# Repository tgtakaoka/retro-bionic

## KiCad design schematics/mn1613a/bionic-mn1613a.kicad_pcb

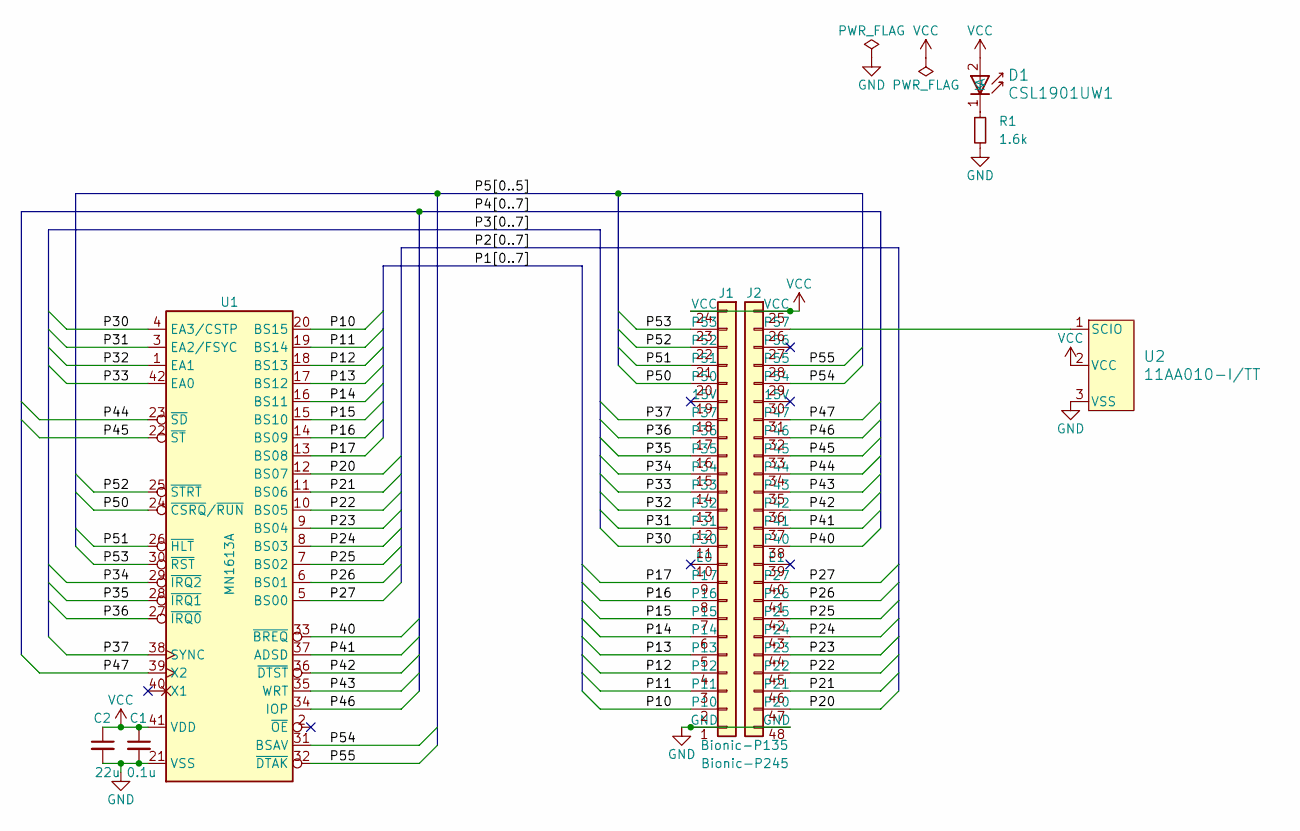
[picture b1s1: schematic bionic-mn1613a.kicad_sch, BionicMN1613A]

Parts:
C1: 0.1u; C_0603_1608Metric_Pad1.08x0.95mm_HandSolder
C2: 22u; C_0603_1608Metric_Pad1.08x0.95mm_HandSolder
D1: CSL1901UW1; LED_CSL1901UW1_ROM-M
J1: Bionic-P135; Bionic-P135_Vertical
J2: Bionic-P245; Bionic-P245_Vertical
R1: 1.6k; R_0603_1608Metric_Pad0.98x0.95mm_HandSolder
U1: MN1613A; DIP-42_W15.24mm_Socket
U2: 11AA010-I/TT; SOT-23_MC_MCH-M

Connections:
/P10: J1.2 (P10), U1.20 (BS15)
/P11: J1.3 (P11), U1.19 (BS14)
/P12: J1.4 (P12), U1.18 (BS13)
/P13: J1.5 (P13), U1.17 (BS12)
/P14: J1.6 (P14), U1.16 (BS11)
/P15: J1.7 (P15), U1.15 (BS10)
/P16: J1.8 (P16), U1.14 (BS09)
/P17: J1.9 (P17), U1.13 (BS08)
/P20: J2.47 (P20), U1.12 (BS07)
/P21: J2.46 (P21), U1.11 (BS06)
/P22: J2.45 (P22), U1.10 (BS05)
/P23: J2.44 (P23), U1.9 (BS04)
/P24: J2.43 (P24), U1.8 (BS03)
/P25: J2.42 (P25), U1.7 (BS02)
/P26: J2.41 (P26), U1.6 (BS01)
/P27: J2.40 (P27), U1.5 (BS00)
/P30: J1.11 (P30), U1.4 (EA3/CSTP)
/P31: J1.12 (P31), U1.3 (EA2/FSYC)
/P32: J1.13 (P32), U1.1 (EA1)
/P33: J1.14 (P33), U1.42 (EA0)
/P34: J1.15 (P34), U1.29 (~IRQ2)
/P35: J1.16 (P35), U1.28 (~IRQ1)
/P36: J1.17 (P36), U1.27 (~IRQ0)
/P37: J1.18 (P37), U1.38 (SYNC)
/P40: J2.38 (P40), U1.33 (~BREQ)
/P41: J2.37 (P41), U1.37 (ADSD)
/P42: J2.36 (P42), U1.36 (~DTST)
/P43: J2.35 (P43), U1.35 (WRT)
/P44: J2.34 (P44), U1.23 (~SD)
/P45: J2.33 (P45), U1.22 (~ST)
/P46: J2.32 (P46), U1.34 (IOP)
/P47: J2.31 (P47), U1.39 (X2)
/P50: J1.20 (P50), U1.24 (~CSRQ/~RUN)
/P51: J1.21 (P51), U1.26 (~HLT)
/P52: J1.22 (P52), U1.25 (~STRT)
/P53: J1.23 (P53), U1.30 (~RST)
/P54: J2.29 (P54), U1.31 (BSAV)
/P55: J2.28 (P55), U1.32 (~DTAK)
GND: C1.2, C2.2, J1.1 (GND), J2.48 (GND), R1.2, U1.21 (VSS), U2.3 (VSS)
unnamed: D1.1 (K), R1.1
unnamed: J2.26 (P57), U2.1 (SCIO)
VCC: C1.1, C2.1, D1.2 (A), J1.24 (VCC), J2.25 (VCC), U1.41 (VDD), U2.2 (VCC)

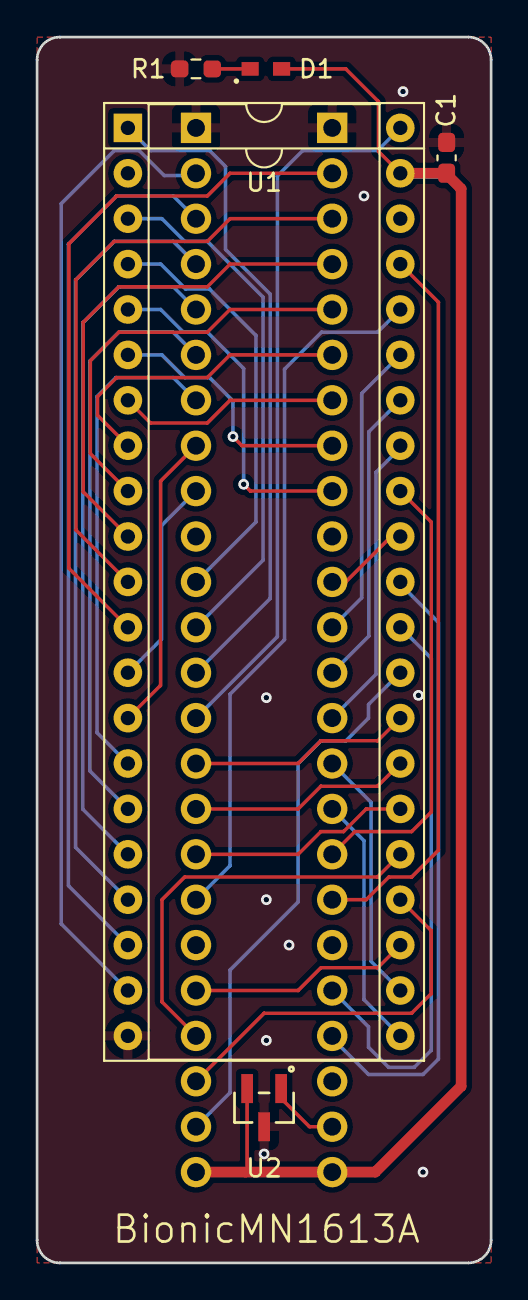
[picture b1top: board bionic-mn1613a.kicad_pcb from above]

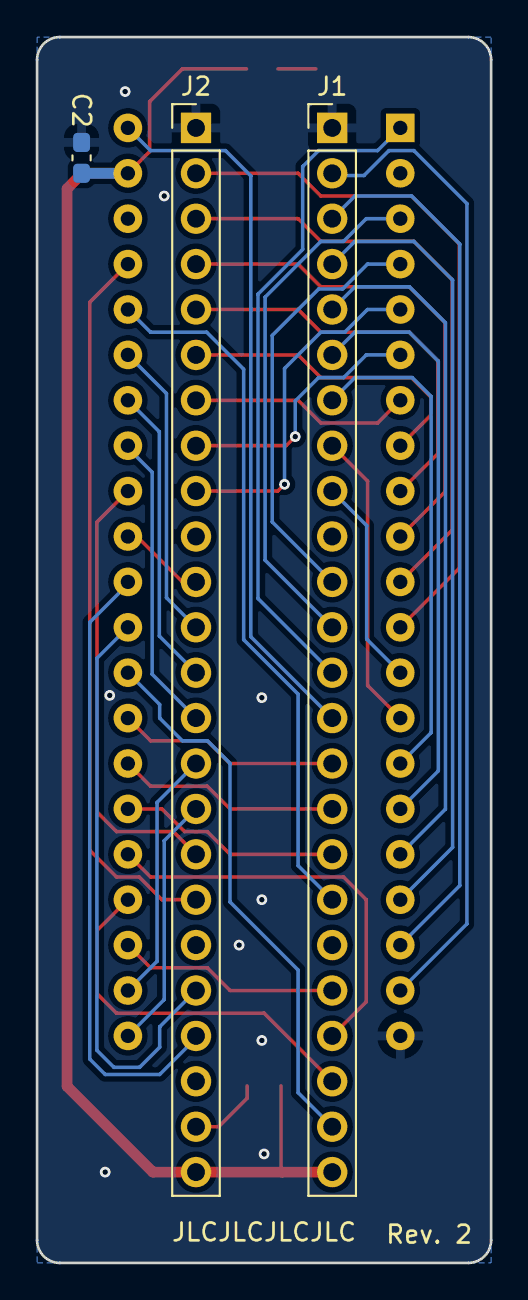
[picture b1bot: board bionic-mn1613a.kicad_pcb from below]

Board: 2 copper layers, 25.4 x 68.6 mm, 8 parts (3 on the bottom side), 42 nets.

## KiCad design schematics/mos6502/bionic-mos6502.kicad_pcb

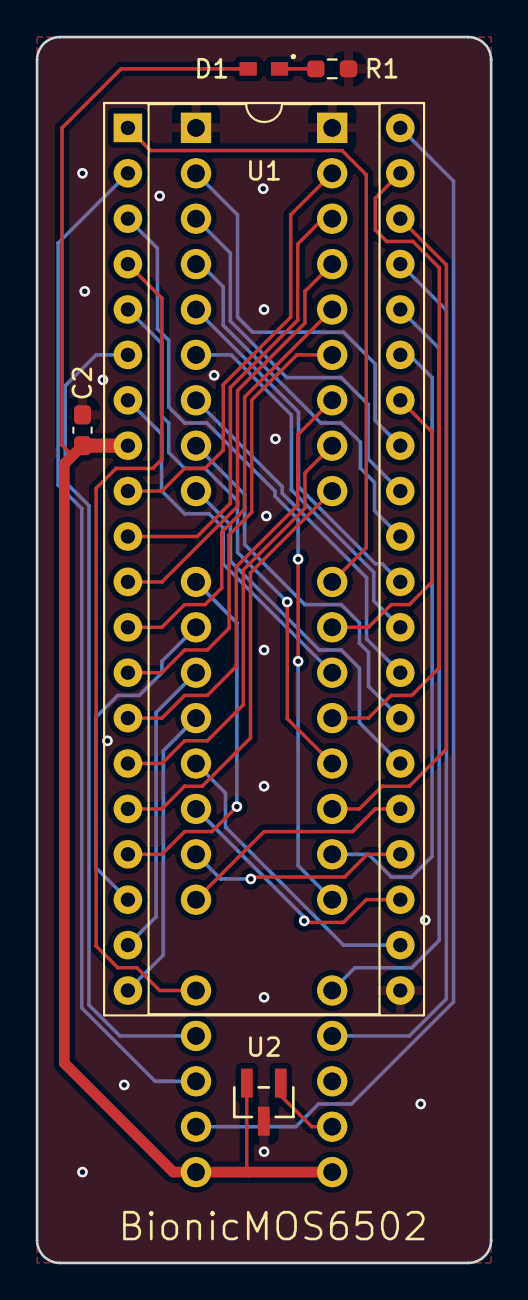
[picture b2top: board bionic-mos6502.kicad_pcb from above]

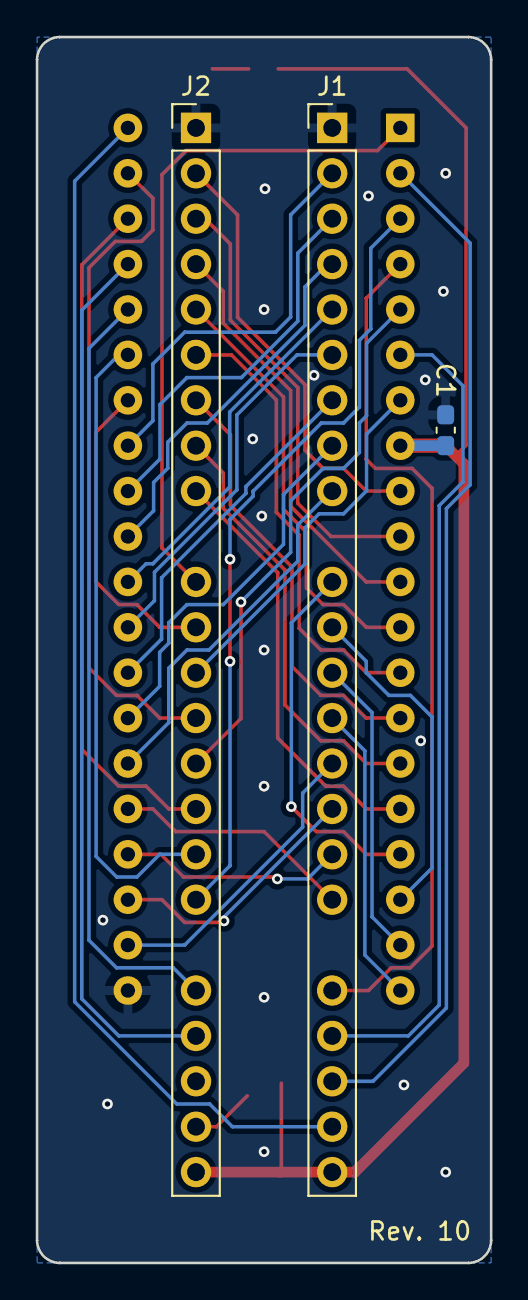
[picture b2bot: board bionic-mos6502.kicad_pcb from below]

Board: 2 copper layers, 25.4 x 68.6 mm, 8 parts (3 on the bottom side), 42 nets.

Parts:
C1: 0.1u; C_0603_1608Metric_Pad1.08x0.95mm_HandSolder
C2: 22u; C_0603_1608Metric_Pad1.08x0.95mm_HandSolder
D1: CSL1901UW1; LED_CSL1901UW1_ROM-M
J1: Bionic-P135; Bionic-P135_THT
J2: Bionic-P245; Bionic-P245_THT
R1: 1.6k; R_0603_1608Metric_Pad0.98x0.95mm_HandSolder
U1: W65C816S; DIP-40_W15.24mm_Socket
U2: 11AA010-I/TT; SOT-23_MC_MCH-M

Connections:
/P10: J1.2 (P10), U1.33 (D0)
/P11: J1.3 (P11), U1.32 (D1)
/P12: J1.4 (P12), U1.31 (D2)
/P13: J1.5 (P13), U1.30 (D3)
/P14: J1.6 (P14), U1.29 (D4)
/P15: J1.7 (P15), U1.28 (D5)
/P16: J1.8 (P16), U1.27 (D6)
/P17: J1.9 (P17), U1.26 (D7)
/P20: J2.47 (P20), U1.9 (A0)
/P21: J2.46 (P21), U1.10 (A1)
/P22: J2.45 (P22), U1.11 (A2)
/P23: J2.44 (P23), U1.12 (A3)
/P24: J2.43 (P24), U1.13 (A4)
/P25: J2.42 (P25), U1.14 (A5)
/P26: J2.41 (P26), U1.15 (A6)
/P27: J2.40 (P27), U1.16 (A7)
/P30: J1.11 (P30), U1.17 (A8)
/P31: J1.12 (P31), U1.18 (A9)
/P32: J1.13 (P32), U1.19 (A10)
/P33: J1.14 (P33), U1.20 (A11)
/P34: J1.15 (P34), U1.22 (A12)
/P35: J1.16 (P35), U1.23 (A13)
/P36: J1.17 (P36), U1.24 (A14)
/P37: J1.18 (P37), U1.25 (A15)
/P40: J2.38 (P40), U1.1 (#VP)
/P41: J2.37 (P41), U1.34 (R/~W)
/P42: J2.36 (P42), U1.7 (VPA)
/P43: J2.35 (P43), U1.39 (VDA)
/P44: J2.34 (P44), U1.5 (#ML)
/P45: J2.33 (P45), U1.38 (MX)
/P46: J2.32 (P46), U1.35 (E)
/P47: J2.31 (P47), U1.3 (~ABORT)
/P50: J1.20 (P50), U1.4 (~IRQ)
/P51: J1.21 (P51), U1.6 (~NMI)
/P52: J1.22 (P52), U1.2 (RDY)
/P53: J1.23 (P53), U1.40 (~RES)
/P54: J2.29 (P54), U1.36 (BE)
/P55: J2.28 (P55), U1.37 (PHI2I)
GND: C1.2, C2.2, J1.1 (GND), J2.48 (GND), R1.2, U1.21 (VSS), U2.3 (VSS)
unnamed: D1.1 (K), R1.1
unnamed: J2.26 (P57), U2.1 (SCIO)
VCC: C1.1, C2.1, D1.2 (A), J1.24 (VCC), J2.25 (VCC), U1.8 (VCC), U2.2 (VCC)

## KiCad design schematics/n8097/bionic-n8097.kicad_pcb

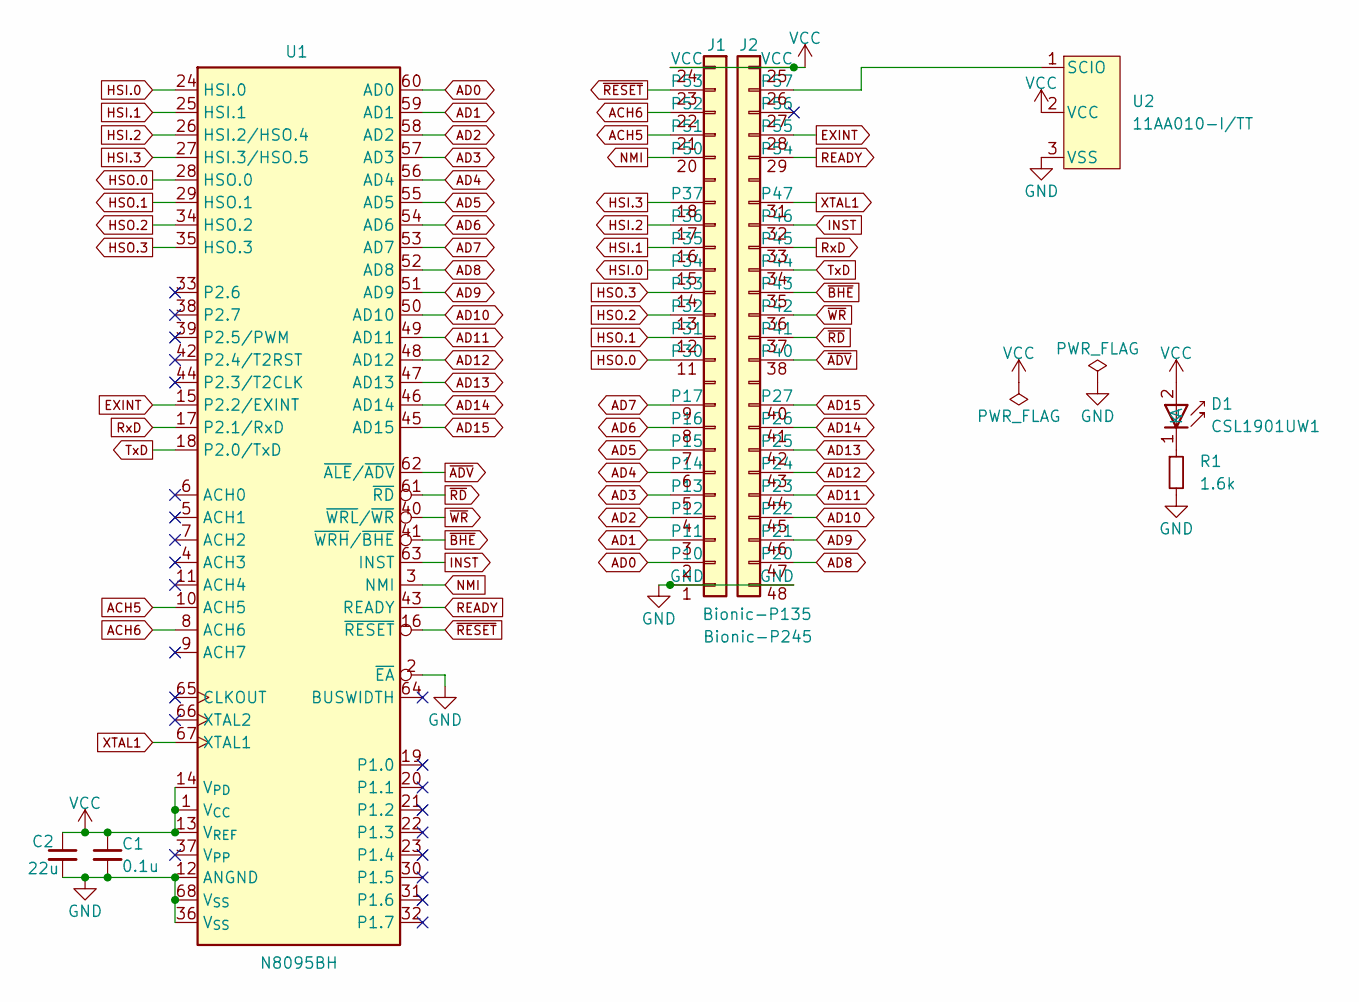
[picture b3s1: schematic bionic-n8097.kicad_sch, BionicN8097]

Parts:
C1: 0.1u; C_0603_1608Metric_Pad1.08x0.95mm_HandSolder
C2: 22u; C_0603_1608Metric_Pad1.08x0.95mm_HandSolder
D1: CSL1901UW1; LED_CSL1901UW1_ROM-M
J1: Bionic-P135; Bionic-P135_SMT
J2: Bionic-P245; Bionic-P245_SMT
R1: 1.6k; R_0603_1608Metric_Pad0.98x0.95mm_HandSolder
U1: N8095BH; 846821B1RKTP
U2: 11AA010-I/TT; SOT-23_MC_MCH-M

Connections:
ACH5: J1.21 (P51), U1.10 (ACH5)
ACH6: J1.22 (P52), U1.8 (ACH6)
AD0: J1.2 (P10), U1.60 (AD0)
AD1: J1.3 (P11), U1.59 (AD1)
AD2: J1.4 (P12), U1.58 (AD2)
AD3: J1.5 (P13), U1.57 (AD3)
AD4: J1.6 (P14), U1.56 (AD4)
AD5: J1.7 (P15), U1.55 (AD5)
AD6: J1.8 (P16), U1.54 (AD6)
AD7: J1.9 (P17), U1.53 (AD7)
AD8: J2.47 (P20), U1.52 (AD8)
AD9: J2.46 (P21), U1.51 (AD9)
AD10: J2.45 (P22), U1.50 (AD10)
AD11: J2.44 (P23), U1.49 (AD11)
AD12: J2.43 (P24), U1.48 (AD12)
AD13: J2.42 (P25), U1.47 (AD13)
AD14: J2.41 (P26), U1.46 (AD14)
AD15: J2.40 (P27), U1.45 (AD15)
EXINT: J2.28 (P55), U1.15 (P2.2/EXINT)
GND: C1.2, C2.2, J1.1 (GND), J2.48 (GND), R1.2, U1.2 (~EA), U1.12 (ANGND), U1.36 (V_{SS}), U1.68 (V_{SS}), U2.3 (VSS)
HSI.0: J1.15 (P34), U1.24 (HSI.0)
HSI.1: J1.16 (P35), U1.25 (HSI.1)
HSI.2: J1.17 (P36), U1.26 (HSI.2/HSO.4)
HSI.3: J1.18 (P37), U1.27 (HSI.3/HSO.5)
HSO.0: J1.11 (P30), U1.28 (HSO.0)
HSO.1: J1.12 (P31), U1.29 (HSO.1)
HSO.2: J1.13 (P32), U1.34 (HSO.2)
HSO.3: J1.14 (P33), U1.35 (HSO.3)
INST: J2.32 (P46), U1.63 (INST)
NMI: J1.20 (P50), U1.3 (NMI)
unnamed: D1.1 (K), R1.1
unnamed: J2.26 (P57), U2.1 (SCIO)
READY: J2.29 (P54), U1.43 (READY)
RxD: J2.33 (P45), U1.17 (P2.1/RxD)
TxD: J2.34 (P44), U1.18 (P2.0/TxD)
VCC: C1.1, C2.1, D1.2 (A), J1.24 (VCC), J2.25 (VCC), U1.1 (V_{CC}), U1.13 (V_{REF}), U1.14 (V_{PD}), U2.2 (VCC)
XTAL1: J2.31 (P47), U1.67 (XTAL1)
~ADV: J2.38 (P40), U1.62 (~ALE/~ADV)
~BHE: J2.35 (P43), U1.41 (~WRH/~BHE)
~RD: J2.37 (P41), U1.61 (~RD)
~RESET: J1.23 (P53), U1.16 (~RESET)
~WR: J2.36 (P42), U1.40 (~WRL/~WR)

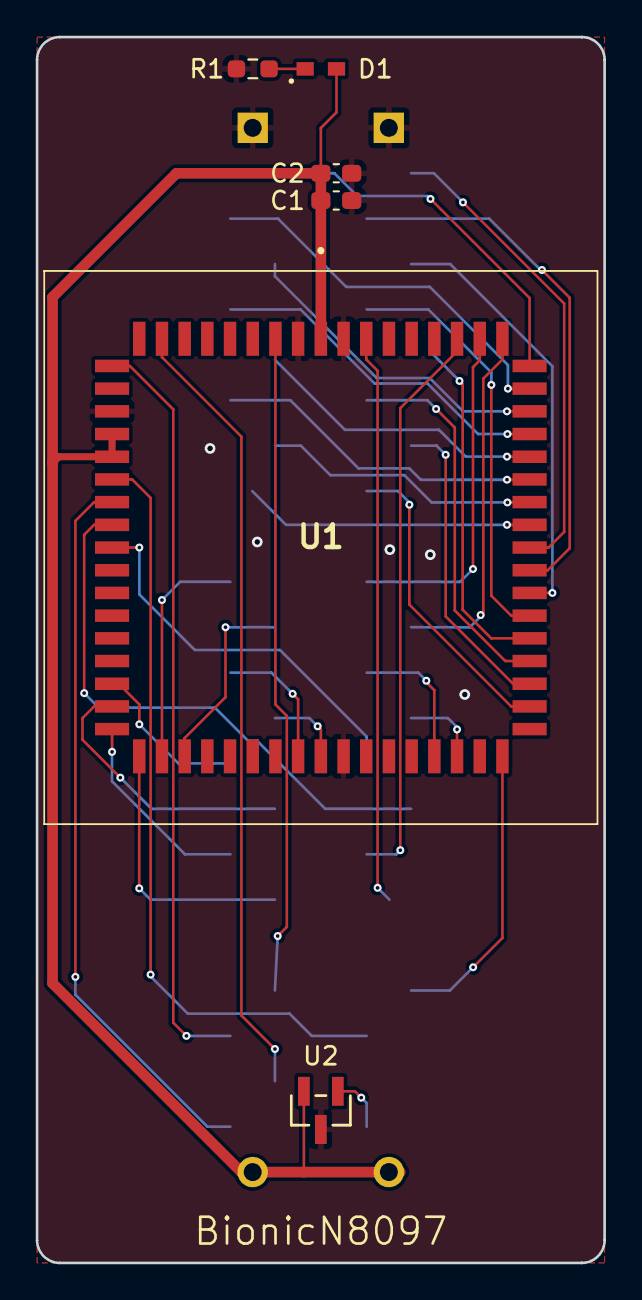
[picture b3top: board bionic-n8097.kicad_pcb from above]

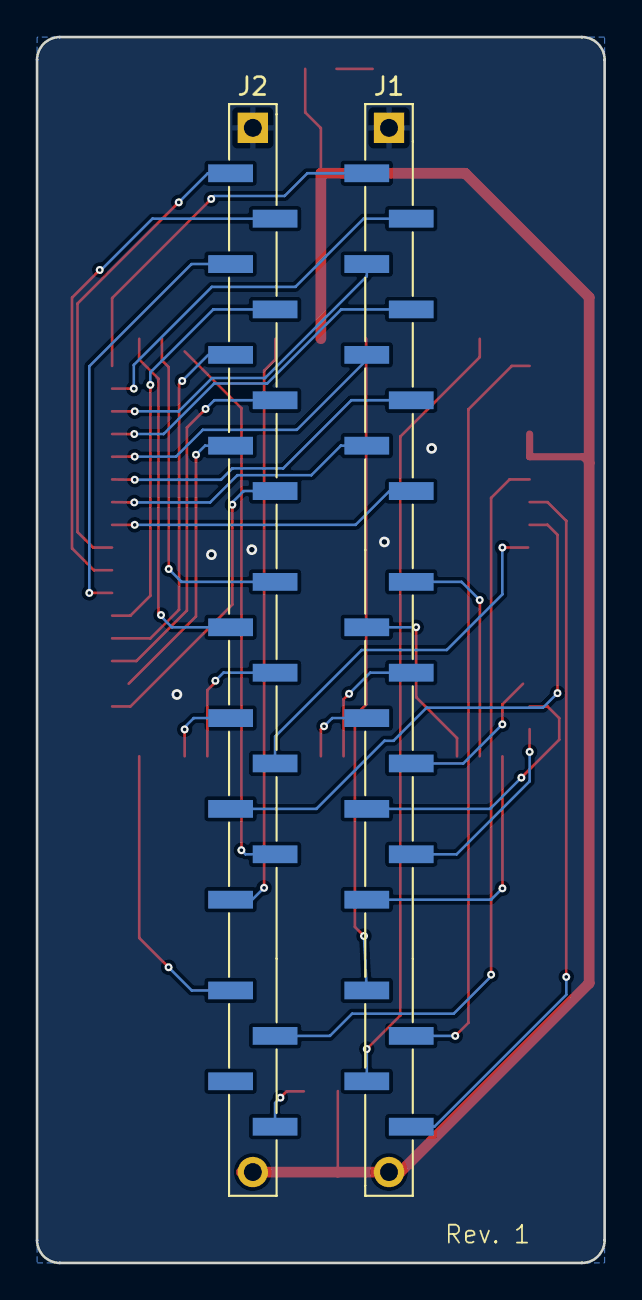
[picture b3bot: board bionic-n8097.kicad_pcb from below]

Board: 2 copper layers, 31.8 x 68.6 mm, 8 parts (2 on the bottom side), 42 nets.

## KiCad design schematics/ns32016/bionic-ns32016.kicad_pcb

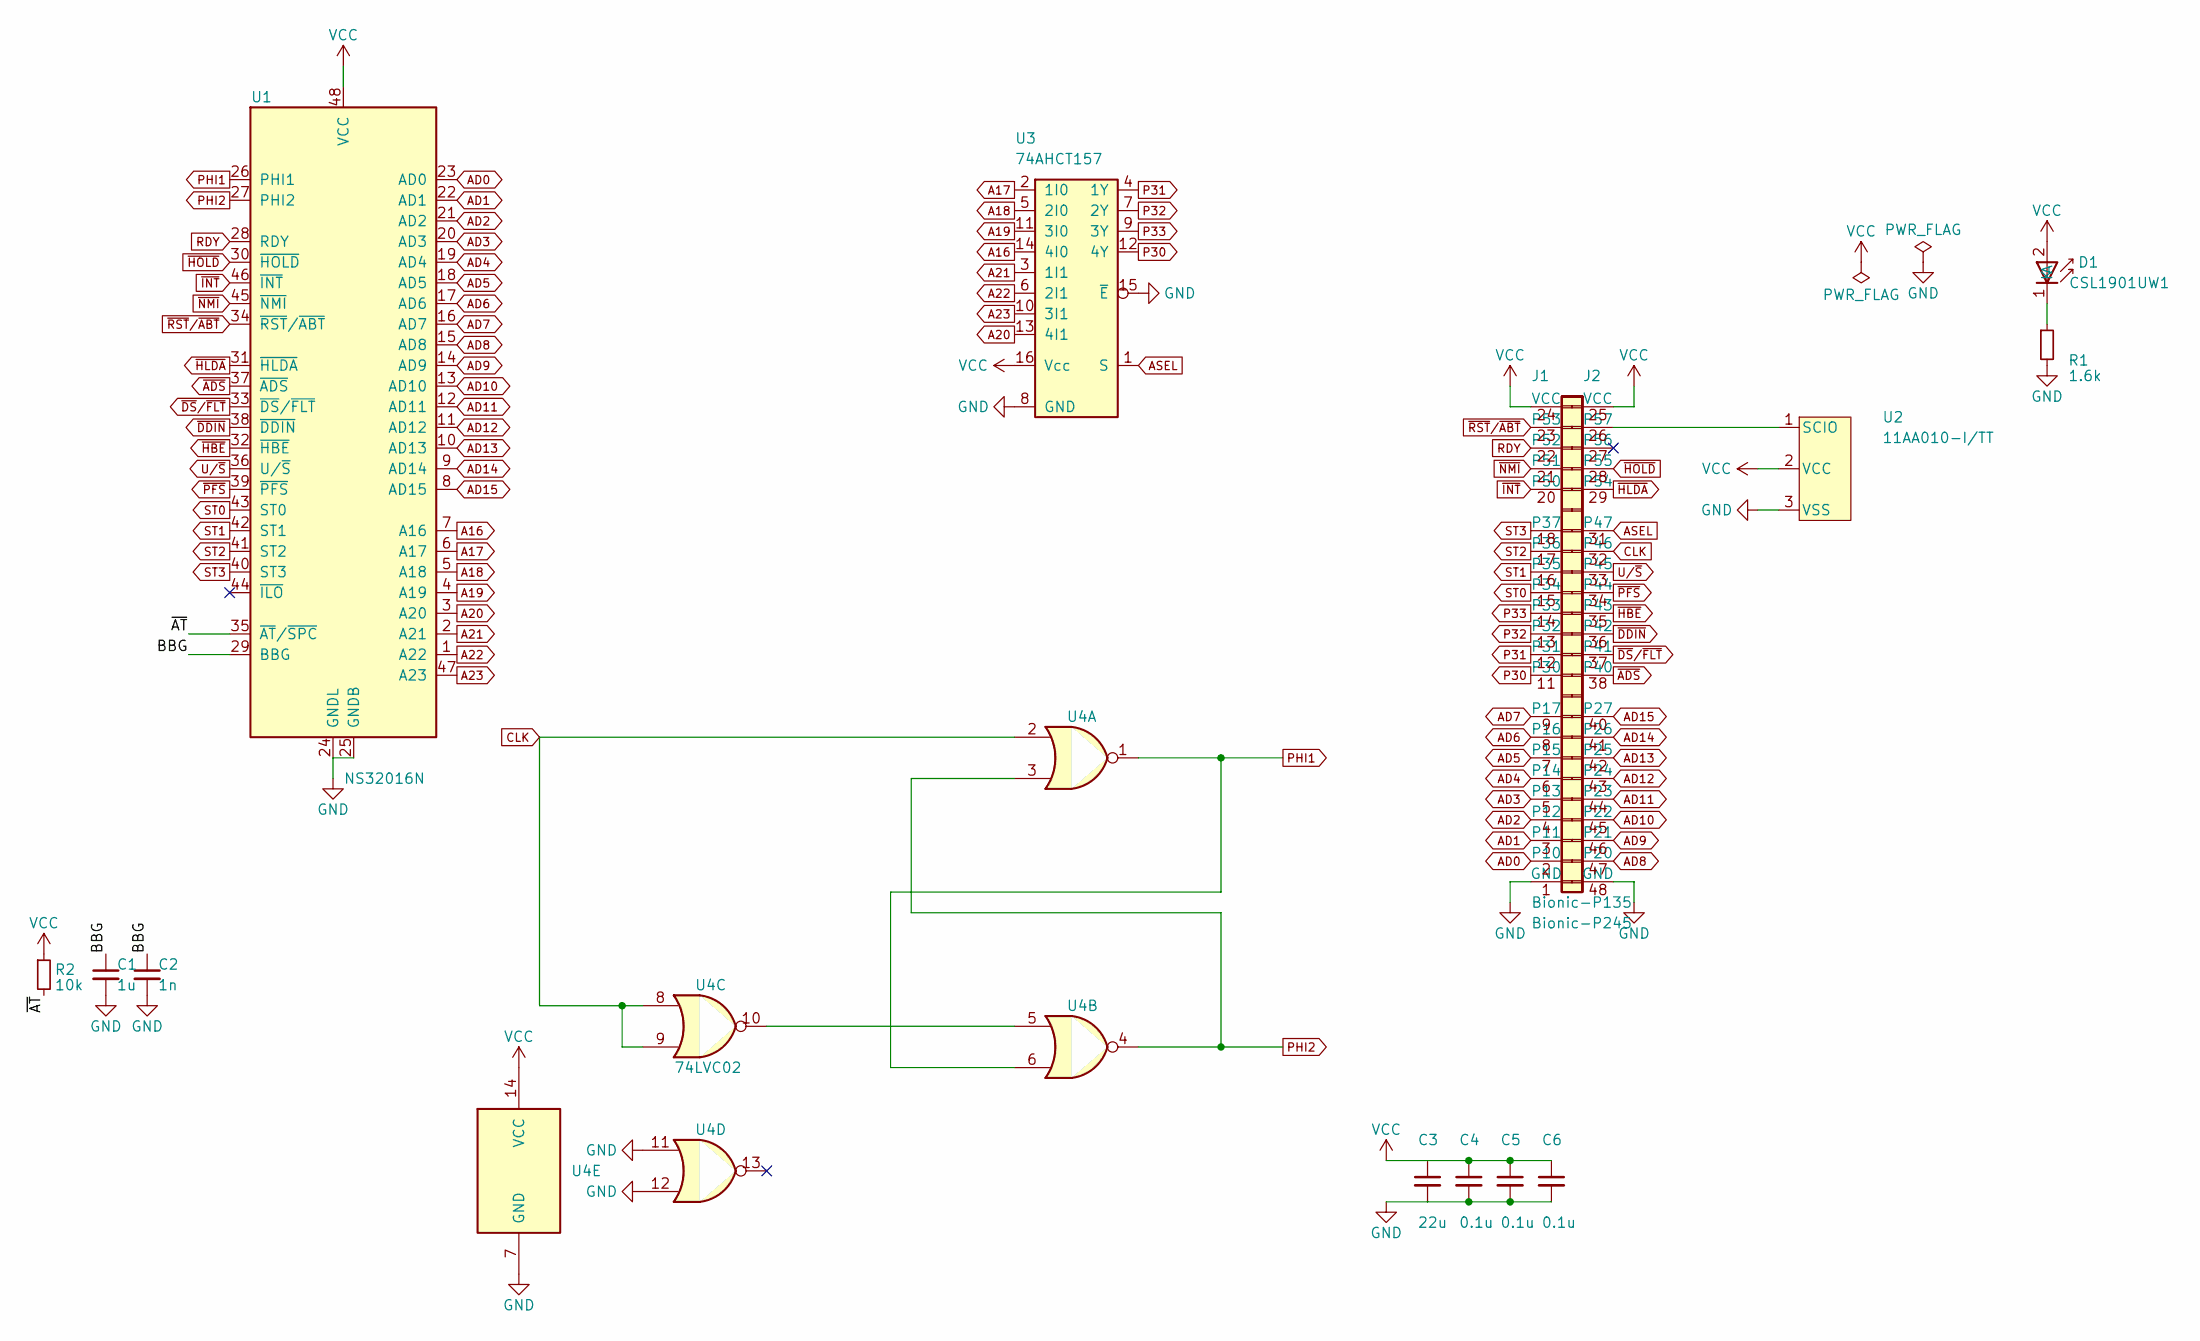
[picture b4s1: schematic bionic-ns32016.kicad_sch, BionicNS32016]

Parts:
C1: 1u; C_0603_1608Metric_Pad1.08x0.95mm_HandSolder
C2: 1n; C_0603_1608Metric_Pad1.08x0.95mm_HandSolder
C3: 22u; C_0603_1608Metric_Pad1.08x0.95mm_HandSolder
C4, C5, C6: 0.1u; C_0603_1608Metric_Pad1.08x0.95mm_HandSolder
D1: CSL1901UW1; LED_CSL1901UW1_ROM-M
J1: Bionic-P135; Bionic-P135_SMT
J2: Bionic-P245; Bionic-P245_SMT
R1: 1.6k; R_0603_1608Metric_Pad0.98x0.95mm_HandSolder
R2: 10k; R_0603_1608Metric_Pad0.98x0.95mm_HandSolder
U1: NS32016N; DIP-48_W15.24mm_Socket
U2: 11AA010-I/TT; SOT-23_MC_MCH-M
U3: 74AHCT157; PW16-M
U4: 74LVC02; PW14-M

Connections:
/BBG: C1.1, C2.1, U1.29 (BBG)
/~AT: R2.2, U1.35 (~AT/~SPC)
A16: U1.7 (A16), U3.14 (4I0)
A17: U1.6 (A17), U3.2 (1I0)
A18: U1.5 (A18), U3.5 (2I0)
A19: U1.4 (A19), U3.11 (3I0)
A20: U1.3 (A20), U3.13 (4I1)
A21: U1.2 (A21), U3.3 (1I1)
A22: U1.1 (A22), U3.6 (2I1)
A23: U1.47 (A23), U3.10 (3I1)
AD0: J1.2 (P10), U1.23 (AD0)
AD1: J1.3 (P11), U1.22 (AD1)
AD2: J1.4 (P12), U1.21 (AD2)
AD3: J1.5 (P13), U1.20 (AD3)
AD4: J1.6 (P14), U1.19 (AD4)
AD5: J1.7 (P15), U1.18 (AD5)
AD6: J1.8 (P16), U1.17 (AD6)
AD7: J1.9 (P17), U1.16 (AD7)
AD8: J2.47 (P20), U1.15 (AD8)
AD9: J2.46 (P21), U1.14 (AD9)
AD10: J2.45 (P22), U1.13 (AD10)
AD11: J2.44 (P23), U1.12 (AD11)
AD12: J2.43 (P24), U1.11 (AD12)
AD13: J2.42 (P25), U1.10 (AD13)
AD14: J2.41 (P26), U1.9 (AD14)
AD15: J2.40 (P27), U1.8 (AD15)
ASEL: J2.31 (P47), U3.1 (S)
CLK: J2.32 (P46), U4.2, U4.8, U4.9
GND: C1.2, C2.2, C3.2, C4.2, C5.2, C6.2, J1.1 (GND), J2.48 (GND), R1.2, U1.24 (GNDL), U1.25 (GNDB), U2.3 (VSS), U3.8 (GND), U3.15 (~E), U4.7 (GND), U4.11, U4.12
unnamed: D1.1 (K), R1.1
unnamed: J2.26 (P57), U2.1 (SCIO)
unnamed: U4.5, U4.10
P30: J1.11 (P30), U3.12 (4Y)
P31: J1.12 (P31), U3.4 (1Y)
P32: J1.13 (P32), U3.7 (2Y)
P33: J1.14 (P33), U3.9 (3Y)
PHI1: U1.26 (PHI1), U4.1, U4.6
PHI2: U1.27 (PHI2), U4.3, U4.4
RDY: J1.22 (P52), U1.28 (RDY)
ST0: J1.15 (P34), U1.43 (ST0)
ST1: J1.16 (P35), U1.42 (ST1)
ST2: J1.17 (P36), U1.41 (ST2)
ST3: J1.18 (P37), U1.40 (ST3)
U/~S: J2.33 (P45), U1.36 (U/~S)
VCC: C3.1, C4.1, C5.1, C6.1, D1.2 (A), J1.24 (VCC), J2.25 (VCC), R2.1, U1.48 (VCC), U2.2 (VCC), U3.16 (Vcc), U4.14 (VCC)
~ADS: J2.38 (P40), U1.37 (~ADS)
~DDIN: J2.36 (P42), U1.38 (~DDIN)
~DS/~FLT: J2.37 (P41), U1.33 (~DS/~FLT)
~HBE: J2.35 (P43), U1.32 (~HBE)
~HLDA: J2.29 (P54), U1.31 (~HLDA)
~HOLD: J2.28 (P55), U1.30 (~HOLD)
~INT: J1.20 (P50), U1.46 (~INT)
~NMI: J1.21 (P51), U1.45 (~NMI)
~PFS: J2.34 (P44), U1.39 (~PFS)
~RST/~ABT: J1.23 (P53), U1.34 (~RST/~ABT)

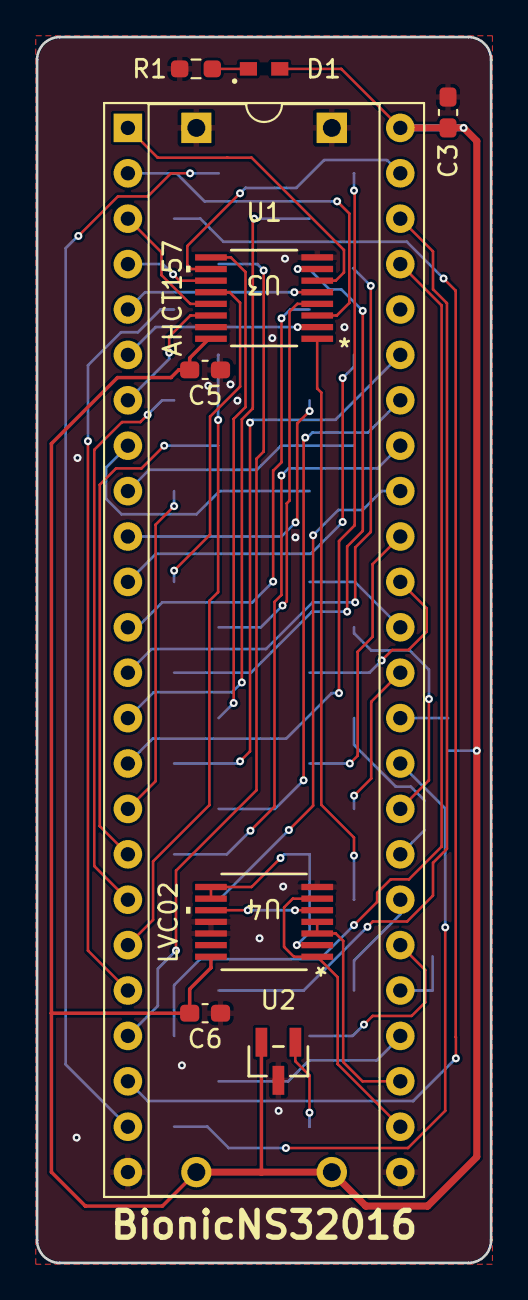
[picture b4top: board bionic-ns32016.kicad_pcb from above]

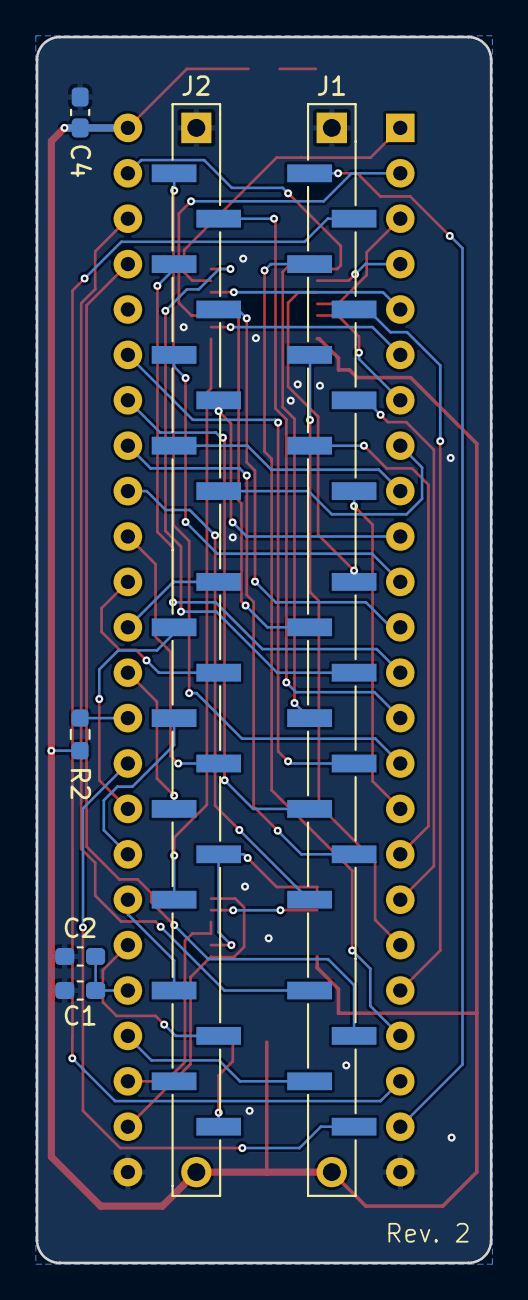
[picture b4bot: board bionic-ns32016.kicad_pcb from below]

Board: 2 copper layers, 25.4 x 68.6 mm, 15 parts (6 on the bottom side), 55 nets.

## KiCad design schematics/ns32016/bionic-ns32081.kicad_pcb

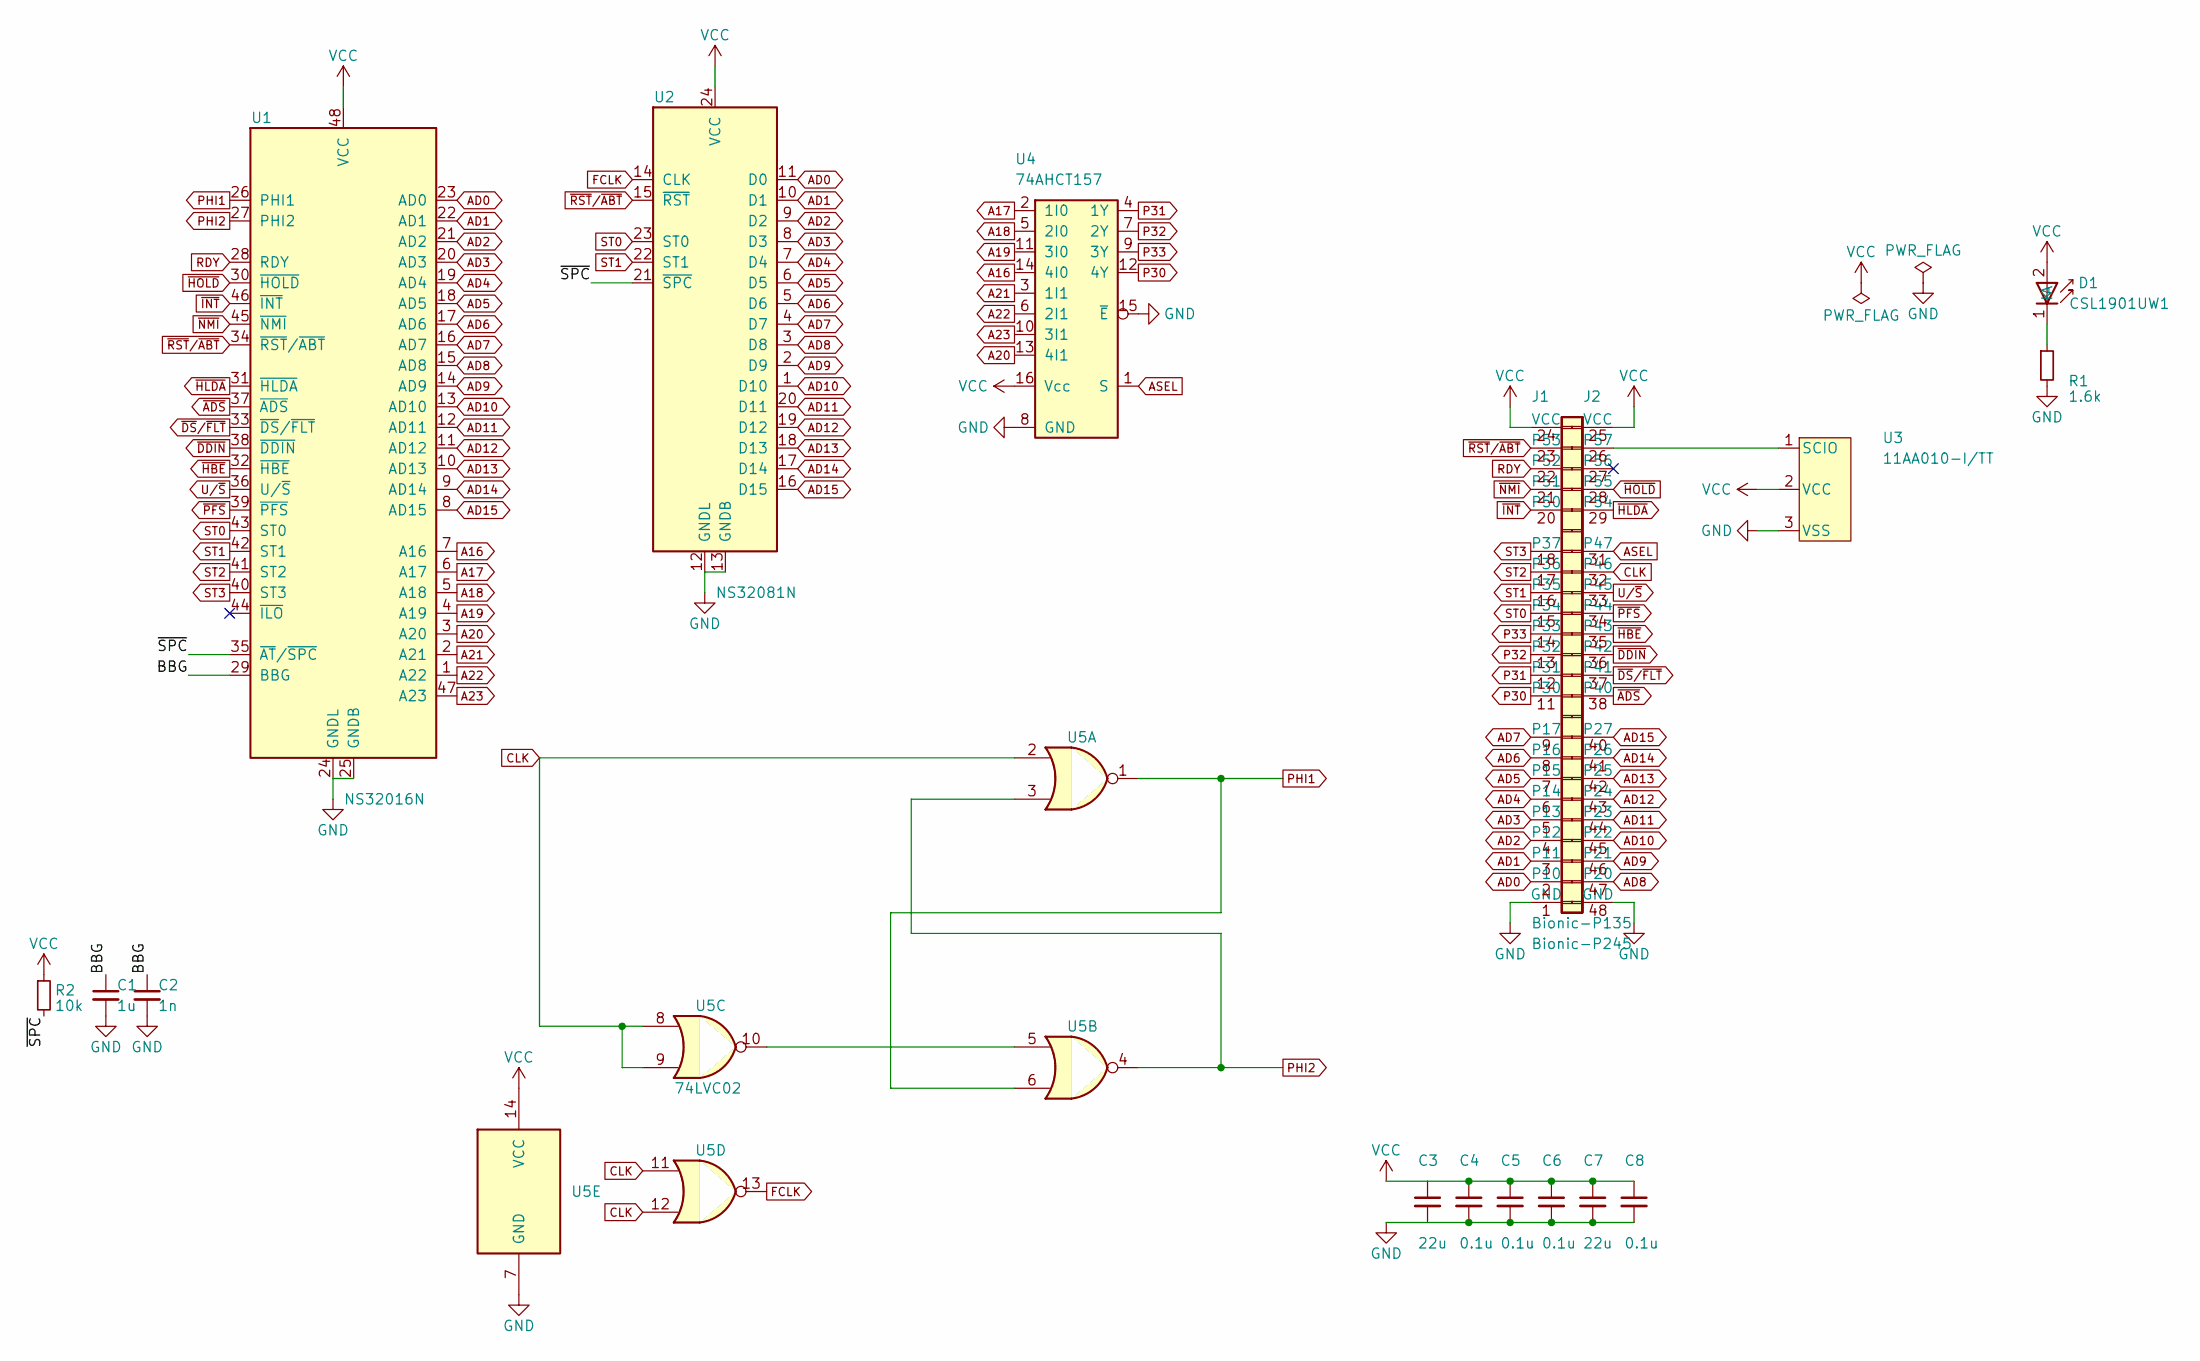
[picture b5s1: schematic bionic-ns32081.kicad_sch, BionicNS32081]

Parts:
C1: 1u; C_0603_1608Metric_Pad1.08x0.95mm_HandSolder
C2: 1n; C_0603_1608Metric_Pad1.08x0.95mm_HandSolder
C3, C7: 22u; C_0603_1608Metric_Pad1.08x0.95mm_HandSolder
C4, C5, C6, C8: 0.1u; C_0603_1608Metric_Pad1.08x0.95mm_HandSolder
D1: CSL1901UW1; LED_CSL1901UW1_ROM-M
J1: Bionic-P135; Bionic-P135_SMT
J2: Bionic-P245; Bionic-P245_SMT
R1: 1.6k; R_0603_1608Metric_Pad0.98x0.95mm_HandSolder
R2: 10k; R_0603_1608Metric_Pad0.98x0.95mm_HandSolder
U1: NS32016N; DIP-48_W15.24mm_Socket
U2: NS32081N; DIP-24_W15.24mm_Socket
U3: 11AA010-I/TT; SOT-23_MC_MCH-M
U4: 74AHCT157; PW16-M
U5: 74LVC02; PW14-M

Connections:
/BBG: C1.1, C2.1, U1.29 (BBG)
/~SPC: R2.2, U1.35 (~AT/~SPC), U2.21 (~SPC)
A16: U1.7 (A16), U4.14 (4I0)
A17: U1.6 (A17), U4.2 (1I0)
A18: U1.5 (A18), U4.5 (2I0)
A19: U1.4 (A19), U4.11 (3I0)
A20: U1.3 (A20), U4.13 (4I1)
A21: U1.2 (A21), U4.3 (1I1)
A22: U1.1 (A22), U4.6 (2I1)
A23: U1.47 (A23), U4.10 (3I1)
AD0: J1.2 (P10), U1.23 (AD0), U2.11 (D0)
AD1: J1.3 (P11), U1.22 (AD1), U2.10 (D1)
AD2: J1.4 (P12), U1.21 (AD2), U2.9 (D2)
AD3: J1.5 (P13), U1.20 (AD3), U2.8 (D3)
AD4: J1.6 (P14), U1.19 (AD4), U2.7 (D4)
AD5: J1.7 (P15), U1.18 (AD5), U2.6 (D5)
AD6: J1.8 (P16), U1.17 (AD6), U2.5 (D6)
AD7: J1.9 (P17), U1.16 (AD7), U2.4 (D7)
AD8: J2.47 (P20), U1.15 (AD8), U2.3 (D8)
AD9: J2.46 (P21), U1.14 (AD9), U2.2 (D9)
AD10: J2.45 (P22), U1.13 (AD10), U2.1 (D10)
AD11: J2.44 (P23), U1.12 (AD11), U2.20 (D11)
AD12: J2.43 (P24), U1.11 (AD12), U2.19 (D12)
AD13: J2.42 (P25), U1.10 (AD13), U2.18 (D13)
AD14: J2.41 (P26), U1.9 (AD14), U2.17 (D14)
AD15: J2.40 (P27), U1.8 (AD15), U2.16 (D15)
ASEL: J2.31 (P47), U4.1 (S)
CLK: J2.32 (P46), U5.2, U5.8, U5.9, U5.11, U5.12
FCLK: U2.14 (CLK), U5.13
GND: C1.2, C2.2, C3.2, C4.2, C5.2, C6.2, C7.2, C8.2, J1.1 (GND), J2.48 (GND), R1.2, U1.24 (GNDL), U1.25 (GNDB), U2.12 (GNDL), U2.13 (GNDB), U3.3 (VSS), U4.8 (GND), U4.15 (~E), U5.7 (GND)
unnamed: D1.1 (K), R1.1
unnamed: J2.26 (P57), U3.1 (SCIO)
unnamed: U5.5, U5.10
P30: J1.11 (P30), U4.12 (4Y)
P31: J1.12 (P31), U4.4 (1Y)
P32: J1.13 (P32), U4.7 (2Y)
P33: J1.14 (P33), U4.9 (3Y)
PHI1: U1.26 (PHI1), U5.1, U5.6
PHI2: U1.27 (PHI2), U5.3, U5.4
RDY: J1.22 (P52), U1.28 (RDY)
ST0: J1.15 (P34), U1.43 (ST0), U2.23 (ST0)
ST1: J1.16 (P35), U1.42 (ST1), U2.22 (ST1)
ST2: J1.17 (P36), U1.41 (ST2)
ST3: J1.18 (P37), U1.40 (ST3)
U/~S: J2.33 (P45), U1.36 (U/~S)
VCC: C3.1, C4.1, C5.1, C6.1, C7.1, C8.1, D1.2 (A), J1.24 (VCC), J2.25 (VCC), R2.1, U1.48 (VCC), U2.24 (VCC), U3.2 (VCC), U4.16 (Vcc), U5.14 (VCC)
~ADS: J2.38 (P40), U1.37 (~ADS)
~DDIN: J2.36 (P42), U1.38 (~DDIN)
~DS/~FLT: J2.37 (P41), U1.33 (~DS/~FLT)
~HBE: J2.35 (P43), U1.32 (~HBE)
~HLDA: J2.29 (P54), U1.31 (~HLDA)
~HOLD: J2.28 (P55), U1.30 (~HOLD)
~INT: J1.20 (P50), U1.46 (~INT)
~NMI: J1.21 (P51), U1.45 (~NMI)
~PFS: J2.34 (P44), U1.39 (~PFS)
~RST/~ABT: J1.23 (P53), U1.34 (~RST/~ABT), U2.15 (~RST)
